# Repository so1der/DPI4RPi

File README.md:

# DPI4RPi

# README:  [Українська](#DPI4RPi-українська) 

**DPI4RPi** is an adapter board designed to connect displays with a DPI (Display Parallel Interface) bus to the Raspberry Pi. This bus is often found in inexpensive displays, such as those from navigation devices, cameras, portable gaming consoles, etc.

The board has been personally tested by me with the T43P12 display.

The board includes a circuit for powering the display’s backlight, with a voltage of **36V** and a current of **20 mA** (approximately up to 8 series connected LEDs). 

> **WARNING:** The circuit does not have an open-circuit protection, so do not connect the board without a display.

The board also features jumpers for HSYNC/VSYNC – some displays can work without them, which frees up the I2C bus. To use HSYNC and VSYNC - short both jumpers to position 1. To use I2C, short both jumpers to position 0 – this will ground the HSYNC and VSYNC, allowing the I2C to be used from the appropriate pins on the board.

---

### Some details about the board:

- Resistors and capacitors are of 0805 package size.
- Inductor size: 4x4mm.
- Diode: BAT54 in SOT-23 package.
- Backlight power IC: LT1937ES5, in TSOT-23 package.
- Display connector: 40-pin FPC, 0.5mm pitch, contacts located ON TOP.
- Raspberry Pi connector: 2x20 pin, 2.54mm pitch.

---

Additionally, you will need to configure the Raspberry Pi to work with DPI. To do this, you need to edit the `/boot/config.txt` file. For more detailed information, you can refer to the following links: [this](https://so1der.github.io/articles/rgb888-to-rpi.html#raspberry-pi-setup) and [this](https://www.zephray.me/post/rpi_dpi/).

Example of use (the board looks a little different in the photos because this is the first revision with some errors that I later fixed):

---

# DPI4RPi Українська:

**DPI4RPi** це плата-адаптер, для підключення дисплеїв з шиною DPI (Display Parallel Interface) до Raspberry Pi. Така шина часто зустрічається в дешевих дисплеях, наприклад з навігаторів, камер, портативних ігрових консолей, тощо.

Плата була протестована особисто мною з дисплеєм T43P12.

На платі присутня схема для живлення підсвітки дисплея напругою **36В** та струмом **20 мА** (приблизно 8 послідовно з'єднаних світлодіодів). 

> **УВАГА:** схема не має захисту від розриву кола, тож не підключайте плату без дисплея.

Також на платі присутні перемички для HSYNC/VSYNC - деякі дисплеї можуть працювати без них, що дозволяє звільнити шину I2C. Щоб використовувати HSYNC та VSYNC - замкніть обидві перемички в положення 1. Щоб використовувати I2C - замкніть обидві перемички в положення 0 - це заземлить HSYNC та VSYNC, і дасть змогу використовувати I2C з відповідних контактів на платі.

---

### Деякі моменти стосовно плати:

- Резистори та конденсатори використані типорозміру 0805.
- Розмір дроселя: 4х4мм.
- Діод: BAT54 в корпусі SOT-23.
- Мікросхема для живлення підсвітки: LT1937ES5, в корпусі TSOT-23.
- Коннектор для дисплея: 40 pin FPC, крок 0.5мм, контакти розташовані ВГОРІ.
- Коннектор для Raspberry Pi: 2x20 pin, крок 2.54мм.

---

Також слід налаштувати Raspberry Pi на роботу з DPI. Для цього треба редагувати файл `/boot/config.txt`. Більш детально можна почитати за [цим](https://so1der.github.io/articles/rgb888-to-rpi.html#raspberry-pi-setup) а також [цим](https://www.zephray.me/post/rpi_dpi/) посиланнями.

Приклад використання (на фотографіях плата трішки відрізняється, бо це перша ревізія з деякими помилками, які я в подальшому виправив):

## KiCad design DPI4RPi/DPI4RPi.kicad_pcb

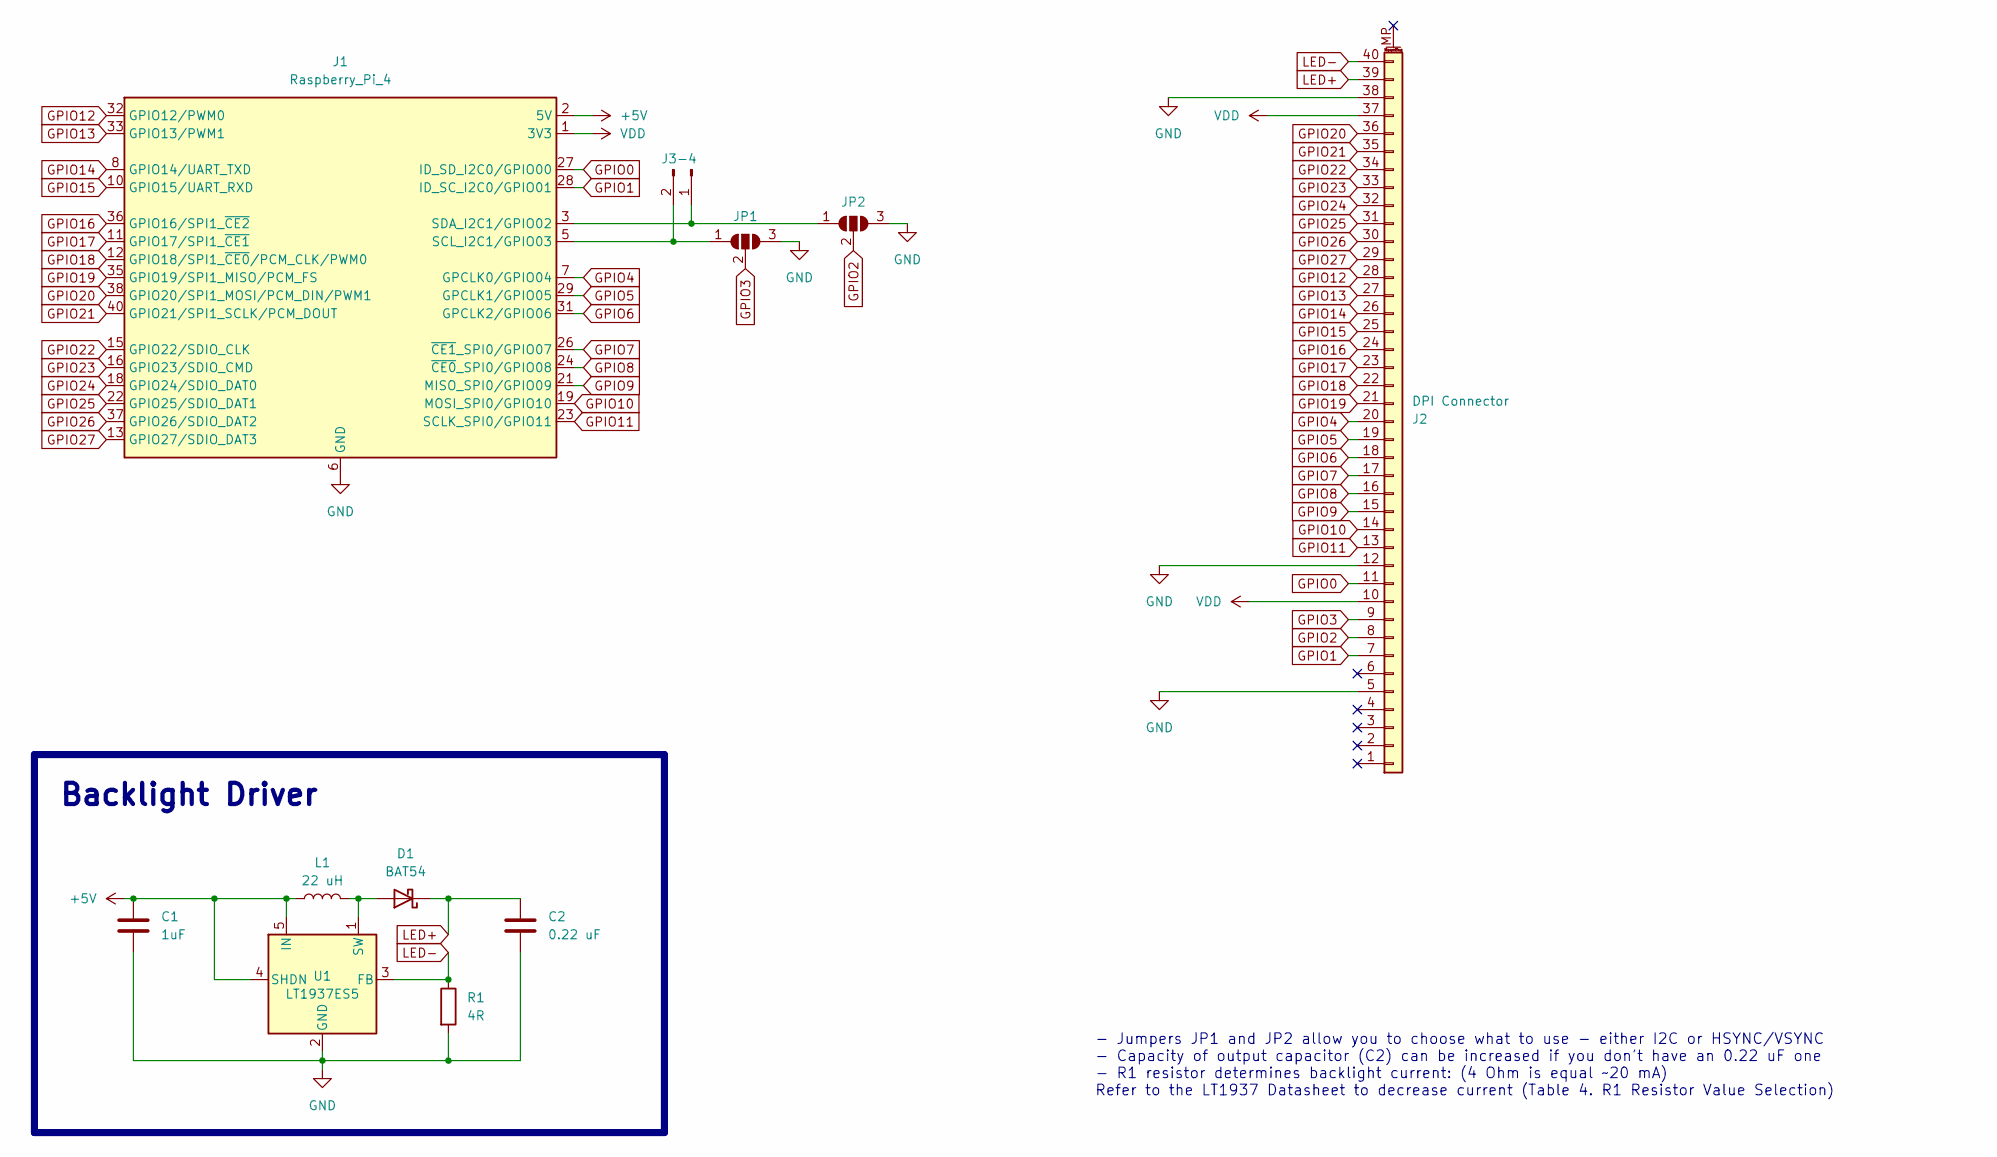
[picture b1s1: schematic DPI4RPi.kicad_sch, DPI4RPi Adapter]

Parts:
C1: 1uF; C_0805_2012Metric_Pad1.18x1.45mm_HandSolder
C2: 0.22 uF; C_0805_2012Metric_Pad1.18x1.45mm_HandSolder
D1: BAT54; SOT-23_Handsoldering
J1: Raspberry_Pi_4; PinSocket_2x20_P2.54mm_Vertical
J2: DPI Connector; Amphenol_F32Q-1A7x1-11040_1x40-1MP_P0.5mm_Horizontal
J3-4: Conn_01x02_Pin; PinHeader_1x02_P2.54mm_Vertical
JP1, JP2: SolderJumper_3_Open; SolderJumper-3_P2.0mm_Open_TrianglePad1.0x1.5mm_NumberLabels
L1: 22 uH; L_Vishay_IFSC-1515AH_4x4x1.8mm
R1: 4R; R_0805_2012Metric_Pad1.20x1.40mm_HandSolder
U1: LT1937ES5; SOT-23-5

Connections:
+5V: C1.1, J1.2 (5V), J1.4 (5V), L1.1, U1.4 (SHDN), U1.5 (IN)
GND: C1.2, C2.2, J1.6 (GND), J1.9 (GND), J1.14 (GND), J1.20 (GND), J1.25 (GND), J1.30 (GND), J1.34 (GND), J1.39 (GND), J2.5, J2.12, J2.38, JP1.3 (B), JP2.3 (B), R1.2, U1.2 (GND)
GPIO0: J1.27 (ID_SD_I2C0/GPIO00), J2.11
GPIO1: J1.28 (ID_SC_I2C0/GPIO01), J2.7
GPIO2: J2.8, JP2.2 (C)
GPIO3: J2.9, JP1.2 (C)
GPIO4: J1.7 (GPCLK0/GPIO04), J2.20
GPIO5: J1.29 (GPCLK1/GPIO05), J2.19
GPIO6: J1.31 (GPCLK2/GPIO06), J2.18
GPIO7: J1.26 (~CE1_SPI0/GPIO07), J2.17
GPIO8: J1.24 (~CE0_SPI0/GPIO08), J2.16
GPIO9: J1.21 (MISO_SPI0/GPIO09), J2.15
GPIO10: J1.19 (MOSI_SPI0/GPIO10), J2.14
GPIO11: J1.23 (SCLK_SPI0/GPIO11), J2.13
GPIO12: J1.32 (GPIO12/PWM0), J2.28
GPIO13: J1.33 (GPIO13/PWM1), J2.27
GPIO14: J1.8 (GPIO14/UART_TXD), J2.26
GPIO15: J1.10 (GPIO15/UART_RXD), J2.25
GPIO16: J1.36 (GPIO16/SPI1_~CE2), J2.24
GPIO17: J1.11 (GPIO17/SPI1_~CE1), J2.23
GPIO18: J1.12 (GPIO18/SPI1_~CE0/PCM_CLK/PWM0), J2.22
GPIO19: J1.35 (GPIO19/SPI1_MISO/PCM_FS), J2.21
GPIO20: J1.38 (GPIO20/SPI1_MOSI/PCM_DIN/PWM1), J2.36
GPIO21: J1.40 (GPIO21/SPI1_SCLK/PCM_DOUT), J2.35
GPIO22: J1.15 (GPIO22/SDIO_CLK), J2.34
GPIO23: J1.16 (GPIO23/SDIO_CMD), J2.33
GPIO24: J1.18 (GPIO24/SDIO_DAT0), J2.32
GPIO25: J1.22 (GPIO25/SDIO_DAT1), J2.31
GPIO26: J1.37 (GPIO26/SDIO_DAT2), J2.30
GPIO27: J1.13 (GPIO27/SDIO_DAT3), J2.29
LED+: C2.1, D1.3 (K), J2.39
LED-: J2.40, R1.1, U1.3 (FB)
unnamed: D1.1 (A), L1.2, U1.1 (SW)
unnamed 33: J1.5 (SCL_I2C1/GPIO03), J3-4.2, JP1.1 (A); also elsewhere on the board
unnamed 34: J1.3 (SDA_I2C1/GPIO02), J3-4.1, JP2.1 (A); also elsewhere on the board
VDD: J1.1 (3V3), J1.17 (3V3), J2.10, J2.37

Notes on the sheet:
- Jumpers JP1 and JP2 allow you to choose what to use - either I2C or HSYNC/VSYNC - Capacity of output capacitor (C2) can be increased if you don't have an 0.22 uF one - R1 resistor determines backlight current: (4 Ohm is equal ~20 mA) Refer to the LT1937 Datasheet to decrease current (Table 4. R1 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
Backlight Driver

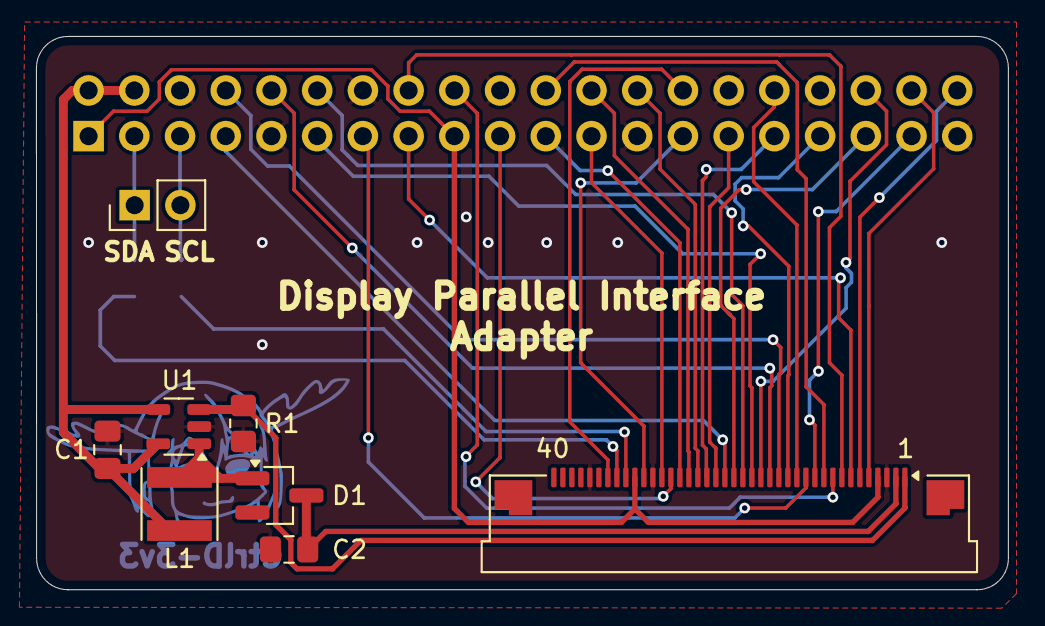
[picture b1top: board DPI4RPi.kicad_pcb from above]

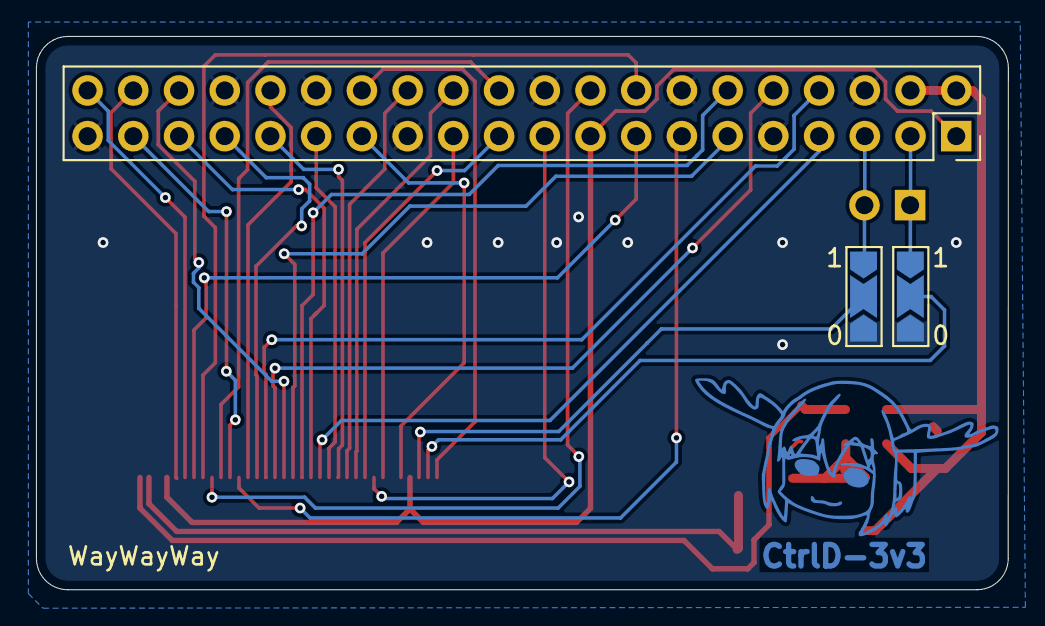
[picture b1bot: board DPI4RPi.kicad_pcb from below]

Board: 2 copper layers, 54.0 x 30.7 mm, 11 parts (3 on the bottom side), 36 nets.

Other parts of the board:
J3: Conn_01x02_Pin; PinHeader_1x02_P2.54mm_Vertical

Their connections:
unnamed 33: J3.2; also elsewhere on the board
unnamed 34: J3.1; also elsewhere on the board

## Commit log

2025-10-07 init commit
